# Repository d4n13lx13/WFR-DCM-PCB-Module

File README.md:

# WFR-DCM-PCB-Module
PCB Module Design

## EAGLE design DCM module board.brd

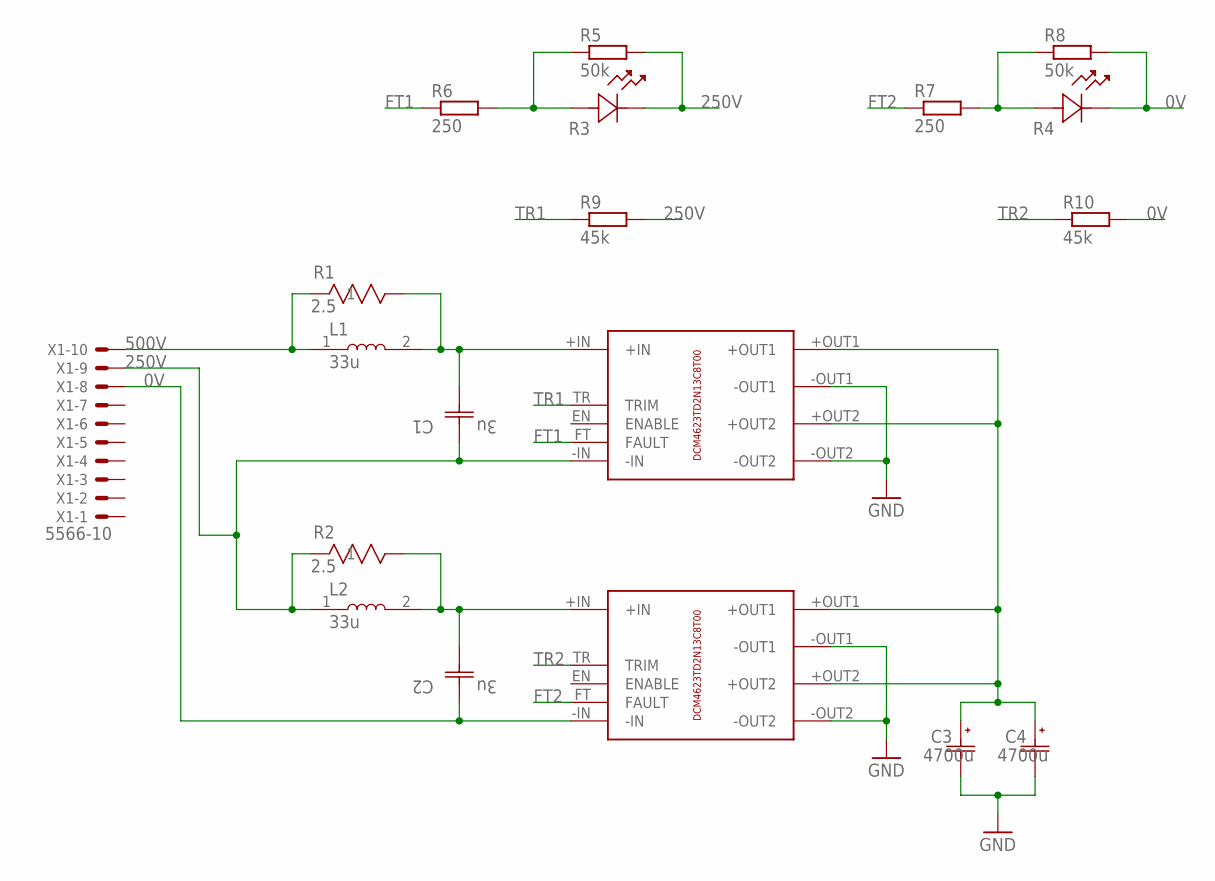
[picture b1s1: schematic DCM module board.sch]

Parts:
C1, C2: 3u; CAP_B58035U5305M062_TDK
C3, C4: 4700u; CAP_UBX_16X25_NCH
L1, L2: 33u; IND_SRP1265A-330M
R1, R2: 2.5; RES_TEH100_OHM
R3, R4: SLR-56VR3F; LED_SLR-56_ROM
R5, R8: 50k; R0805
R6, R7: 250; R0805
R9, R10: 45k; R0805
U$1, U$2: DCM4623TD2N13C8T00
X1: 5566-10

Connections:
0V: C2.1, R4.1, R8.2, R10.2, U$2.-IN, X1.8
250V: C1.1, L2.1, R2.1, R3.1, R5.2, R9.2, U$1.-IN, X1.9
500V: L1.1, R1.1, X1.10
FT1: R6.1, U$1.FT (FAULT)
FT2: R7.1, U$2.FT (FAULT)
GND: C3.2, C4.2, U$1.-OUT1, U$1.-OUT2, U$2.-OUT1, U$2.-OUT2
unnamed: C1.2, L1.2, R1.3 (2), U$1.+IN
unnamed: C3.1, C4.1, U$1.+OUT1, U$1.+OUT2, U$2.+OUT1, U$2.+OUT2
unnamed: C2.2, L2.2, R2.3 (2), U$2.+IN
unnamed: R3.2, R5.1, R6.2
unnamed: R4.2, R7.2, R8.1
TR1: R9.1, U$1.TR (TRIM)
TR2: R10.1, U$2.TR (TRIM)

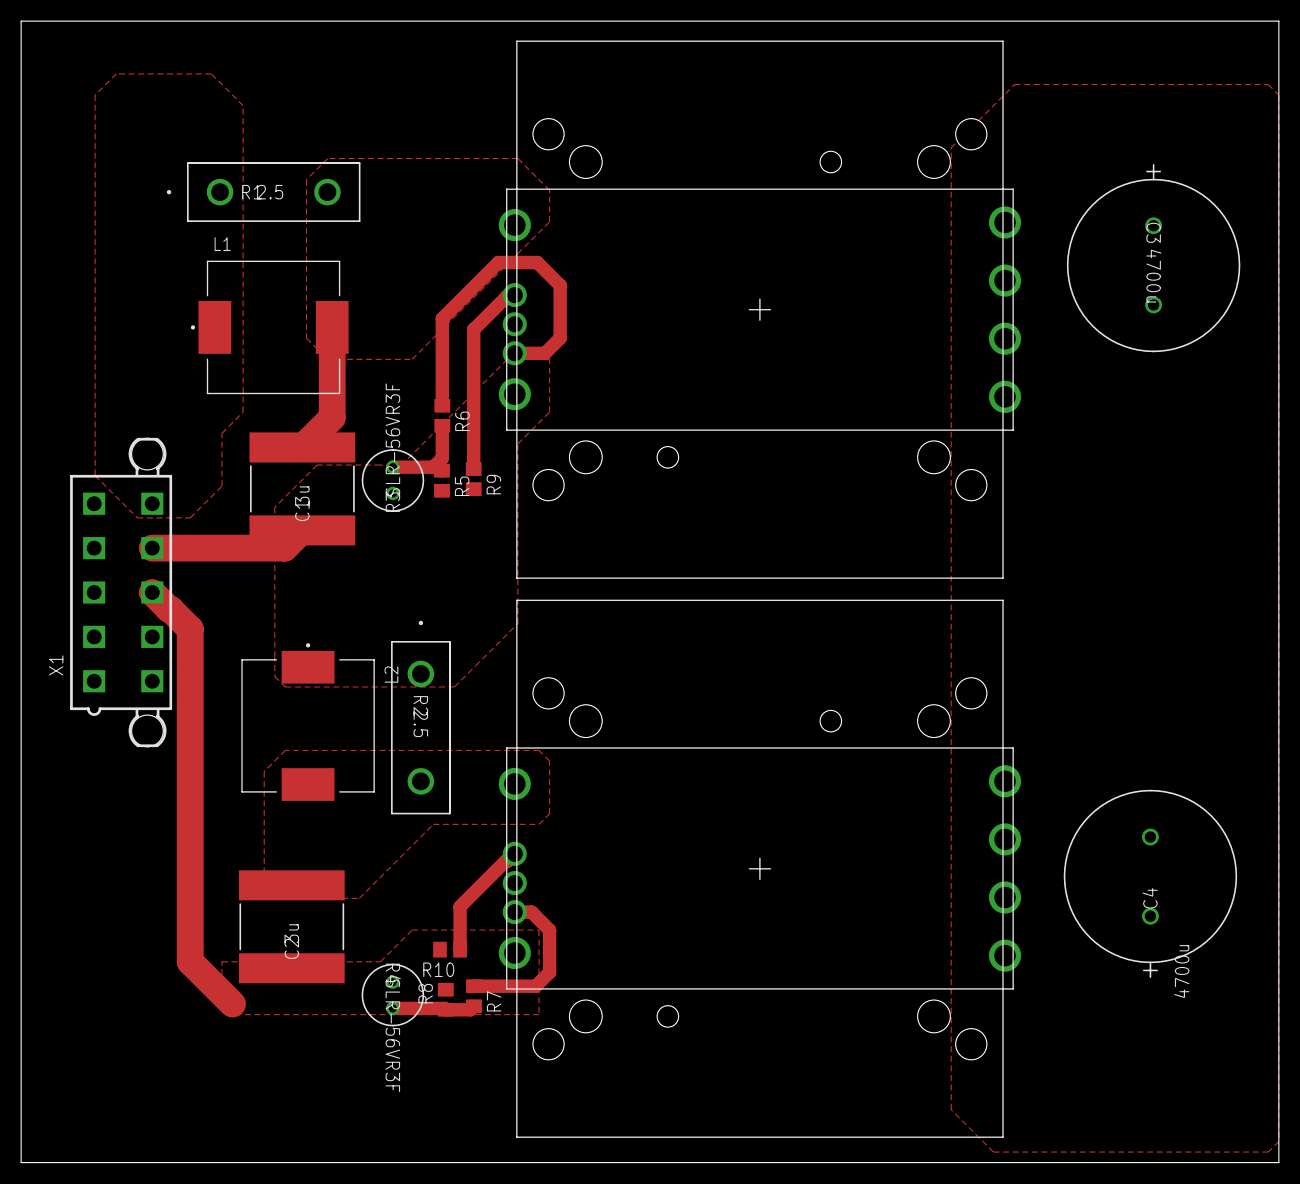
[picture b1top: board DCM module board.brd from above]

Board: 2 copper layers, 119.0 x 108.0 mm, 21 parts (0 on the bottom side), 13 nets.

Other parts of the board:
U$3, U$4: 1102-40408-ND

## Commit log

2020-11-12 Add files via upload
    0.9V
    To add - FT circuit, TR circuit
2020-11-12 Add files via upload
    Version 0.9.1
    Slightly changed symbol for DCDC converter
    To add - FT circuit (Rseries, Rshunt, LED), TR circuit (Resistor)
2020-11-17 Add files via upload
    Version 1.0
    - FT, TR circuits added
    To complete: PCB layout
2020-11-17 Add files via upload
    Version 1.1
    Changes - changed grounds of FT, TR pin circuits to IN-
2020-11-25 Add files via upload
    DCD Board version 1.0
2020-11-26 Add files via upload
    Version 1.1
    - Modified power planes for high-voltage side.

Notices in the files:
parts and their libraries:
COPYRIGHT: Copyright (C) 2018 Accelerated Designs. All rights reserved
